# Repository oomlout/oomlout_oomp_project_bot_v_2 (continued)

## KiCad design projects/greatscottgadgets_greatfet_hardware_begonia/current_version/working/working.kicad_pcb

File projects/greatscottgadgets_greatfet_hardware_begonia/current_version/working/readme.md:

# greatfet_hardware
 
## summary 
* id: greatscottgadgets_greatfet_hardware_begonia
* user: greatscottgadgets
* name: greatfet_hardware
* board: begonia
* repo: https://github.com/greatscottgadgets/greatfet-hardware
* src_file_repo_kicad_pcb: begonia/begonia.kicad_pcb
* src_file_repo_kicad_pcb_link: https://github.com/greatscottgadgets/greatfet-hardware/tree/master/begonia/begonia.kicad_pcb

* src_file_repo_sch: begonia/begonia.sch
* src_file_repo_sch_link: https://github.com/greatscottgadgets/greatfet-hardware/tree/master/begonia/begonia.sch
* full details link: https://github.com/oomlout/oomlout_oomp_project_bot_v_2/tree/main/projects/greatscottgadgets_greatfet_hardware_begonia/current_version/working

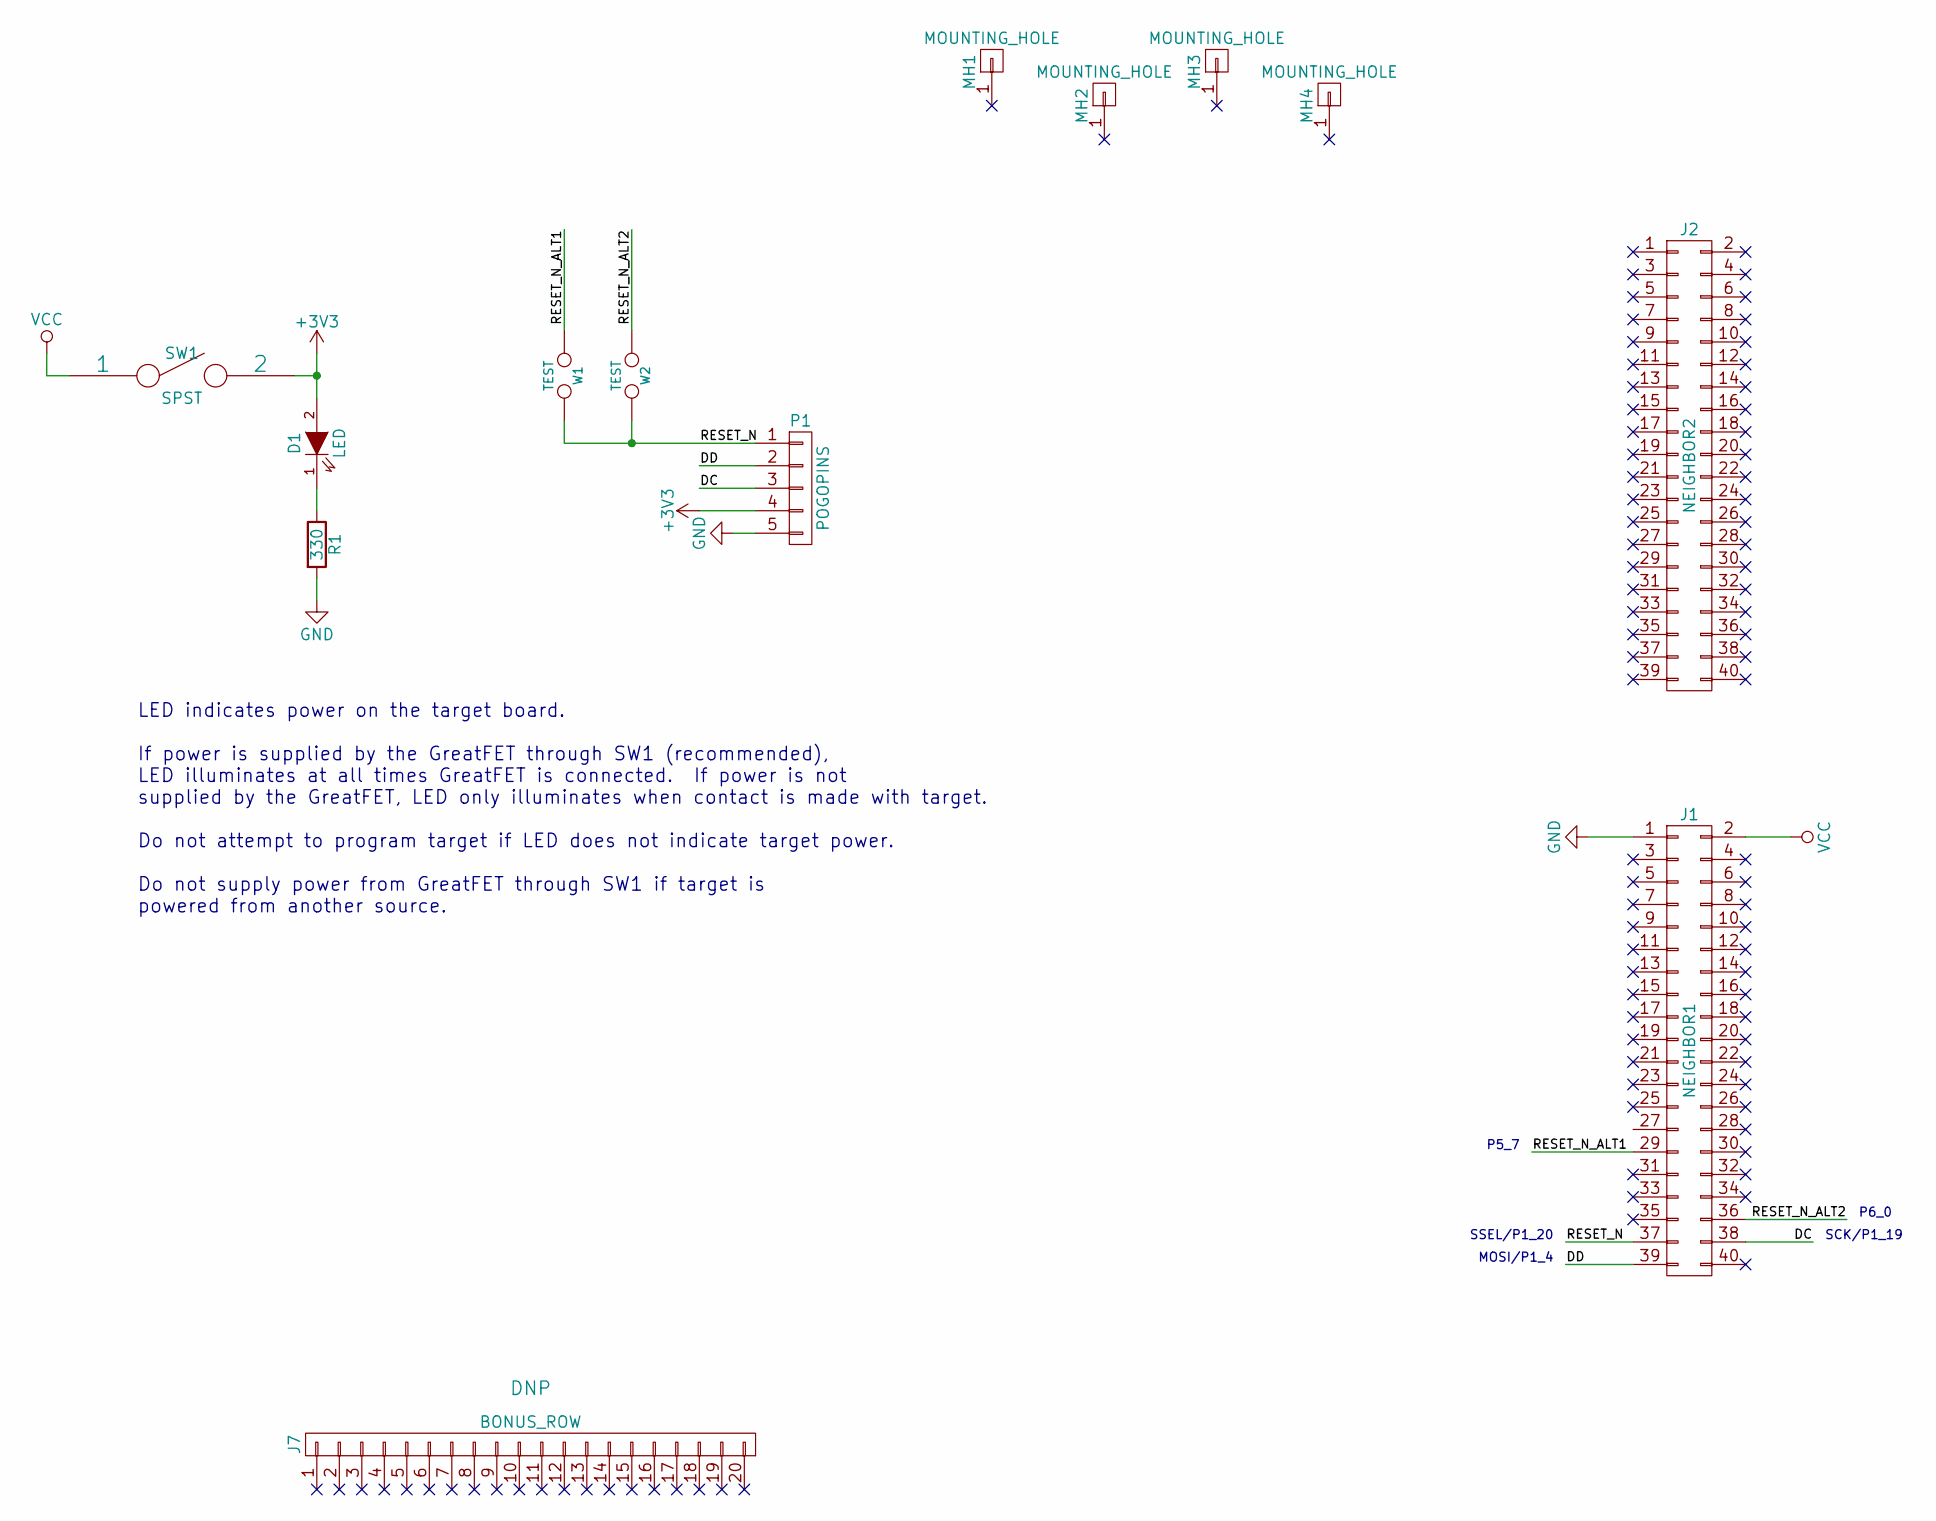
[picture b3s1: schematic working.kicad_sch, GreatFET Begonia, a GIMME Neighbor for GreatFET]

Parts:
D1: LED; 0603D; Part Number APT1608SGC
J1: NEIGHBOR1; HEADER-2x20; Part Number SSQ-120-23-G-D
J2: NEIGHBOR2; HEADER-2x20; Part Number SSQ-120-23-G-D
J7: BONUS_ROW; HEADER-1x20; Part Number SSQ-120-23-G-S
MH1, MH2, MH3, MH4: MOUNTING_HOLE; HOLE126MIL-COPPER
P1: POGOPINS; POGOPIN-5-IMME; Part Number PRT-09174
R1: 330; 0603; Part Number RMCF0603JT330R
SW1: SPST; SSSS810701; Part Number SSSS810701
W1, W2: TEST; 0603-JUMPER

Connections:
+3V3: D1.2 (A), P1.4, SW1.2
/DC: J1.38, P1.3
/DD: J1.39, P1.2
/RESET_N: J1.37, P1.1, W1.2, W2.2
/RESET_N_ALT1: J1.29, W1.1
/RESET_N_ALT2: J1.36, W2.1
GND: J1.1, P1.5, R1.2
unnamed: D1.1 (K), R1.1
VCC: J1.2, SW1.1

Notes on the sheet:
SSEL/P1_20
P6_0
P5_7
MOSI/P1_4
SCK/P1_19
LED indicates power on the target board. If power is supplied by the GreatFET through SW1 (recommended), LED illuminates at all times GreatFET is connected. If power is not supplied by the GreatFET, LED only illuminates when contact is made with target. Do not attempt to program target if LED does 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

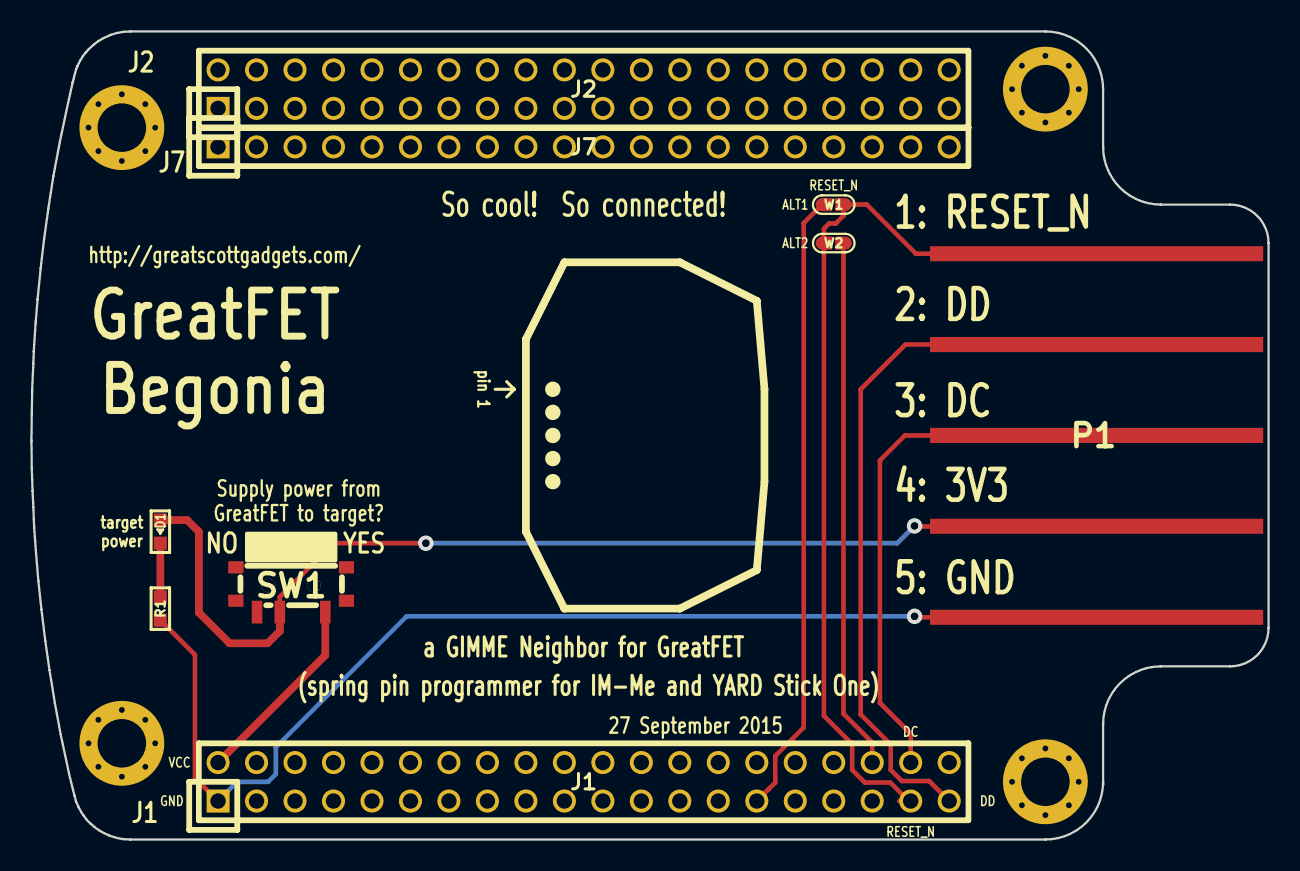
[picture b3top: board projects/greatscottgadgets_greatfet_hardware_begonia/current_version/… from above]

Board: 2 copper layers, 81.7 x 53.3 mm, 13 parts (0 on the bottom side), 9 nets.

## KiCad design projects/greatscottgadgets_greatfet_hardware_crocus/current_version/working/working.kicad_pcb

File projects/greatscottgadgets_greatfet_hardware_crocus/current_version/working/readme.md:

# greatfet_hardware
 
## summary 
* id: greatscottgadgets_greatfet_hardware_crocus
* user: greatscottgadgets
* name: greatfet_hardware
* board: crocus
* repo: https://github.com/greatscottgadgets/greatfet-hardware
* src_file_repo_kicad_pcb: crocus/crocus.kicad_pcb
* src_file_repo_kicad_pcb_link: https://github.com/greatscottgadgets/greatfet-hardware/tree/master/crocus/crocus.kicad_pcb

* src_file_repo_sch: crocus/crocus.sch
* src_file_repo_sch_link: https://github.com/greatscottgadgets/greatfet-hardware/tree/master/crocus/crocus.sch
* full details link: https://github.com/oomlout/oomlout_oomp_project_bot_v_2/tree/main/projects/greatscottgadgets_greatfet_hardware_crocus/current_version/working

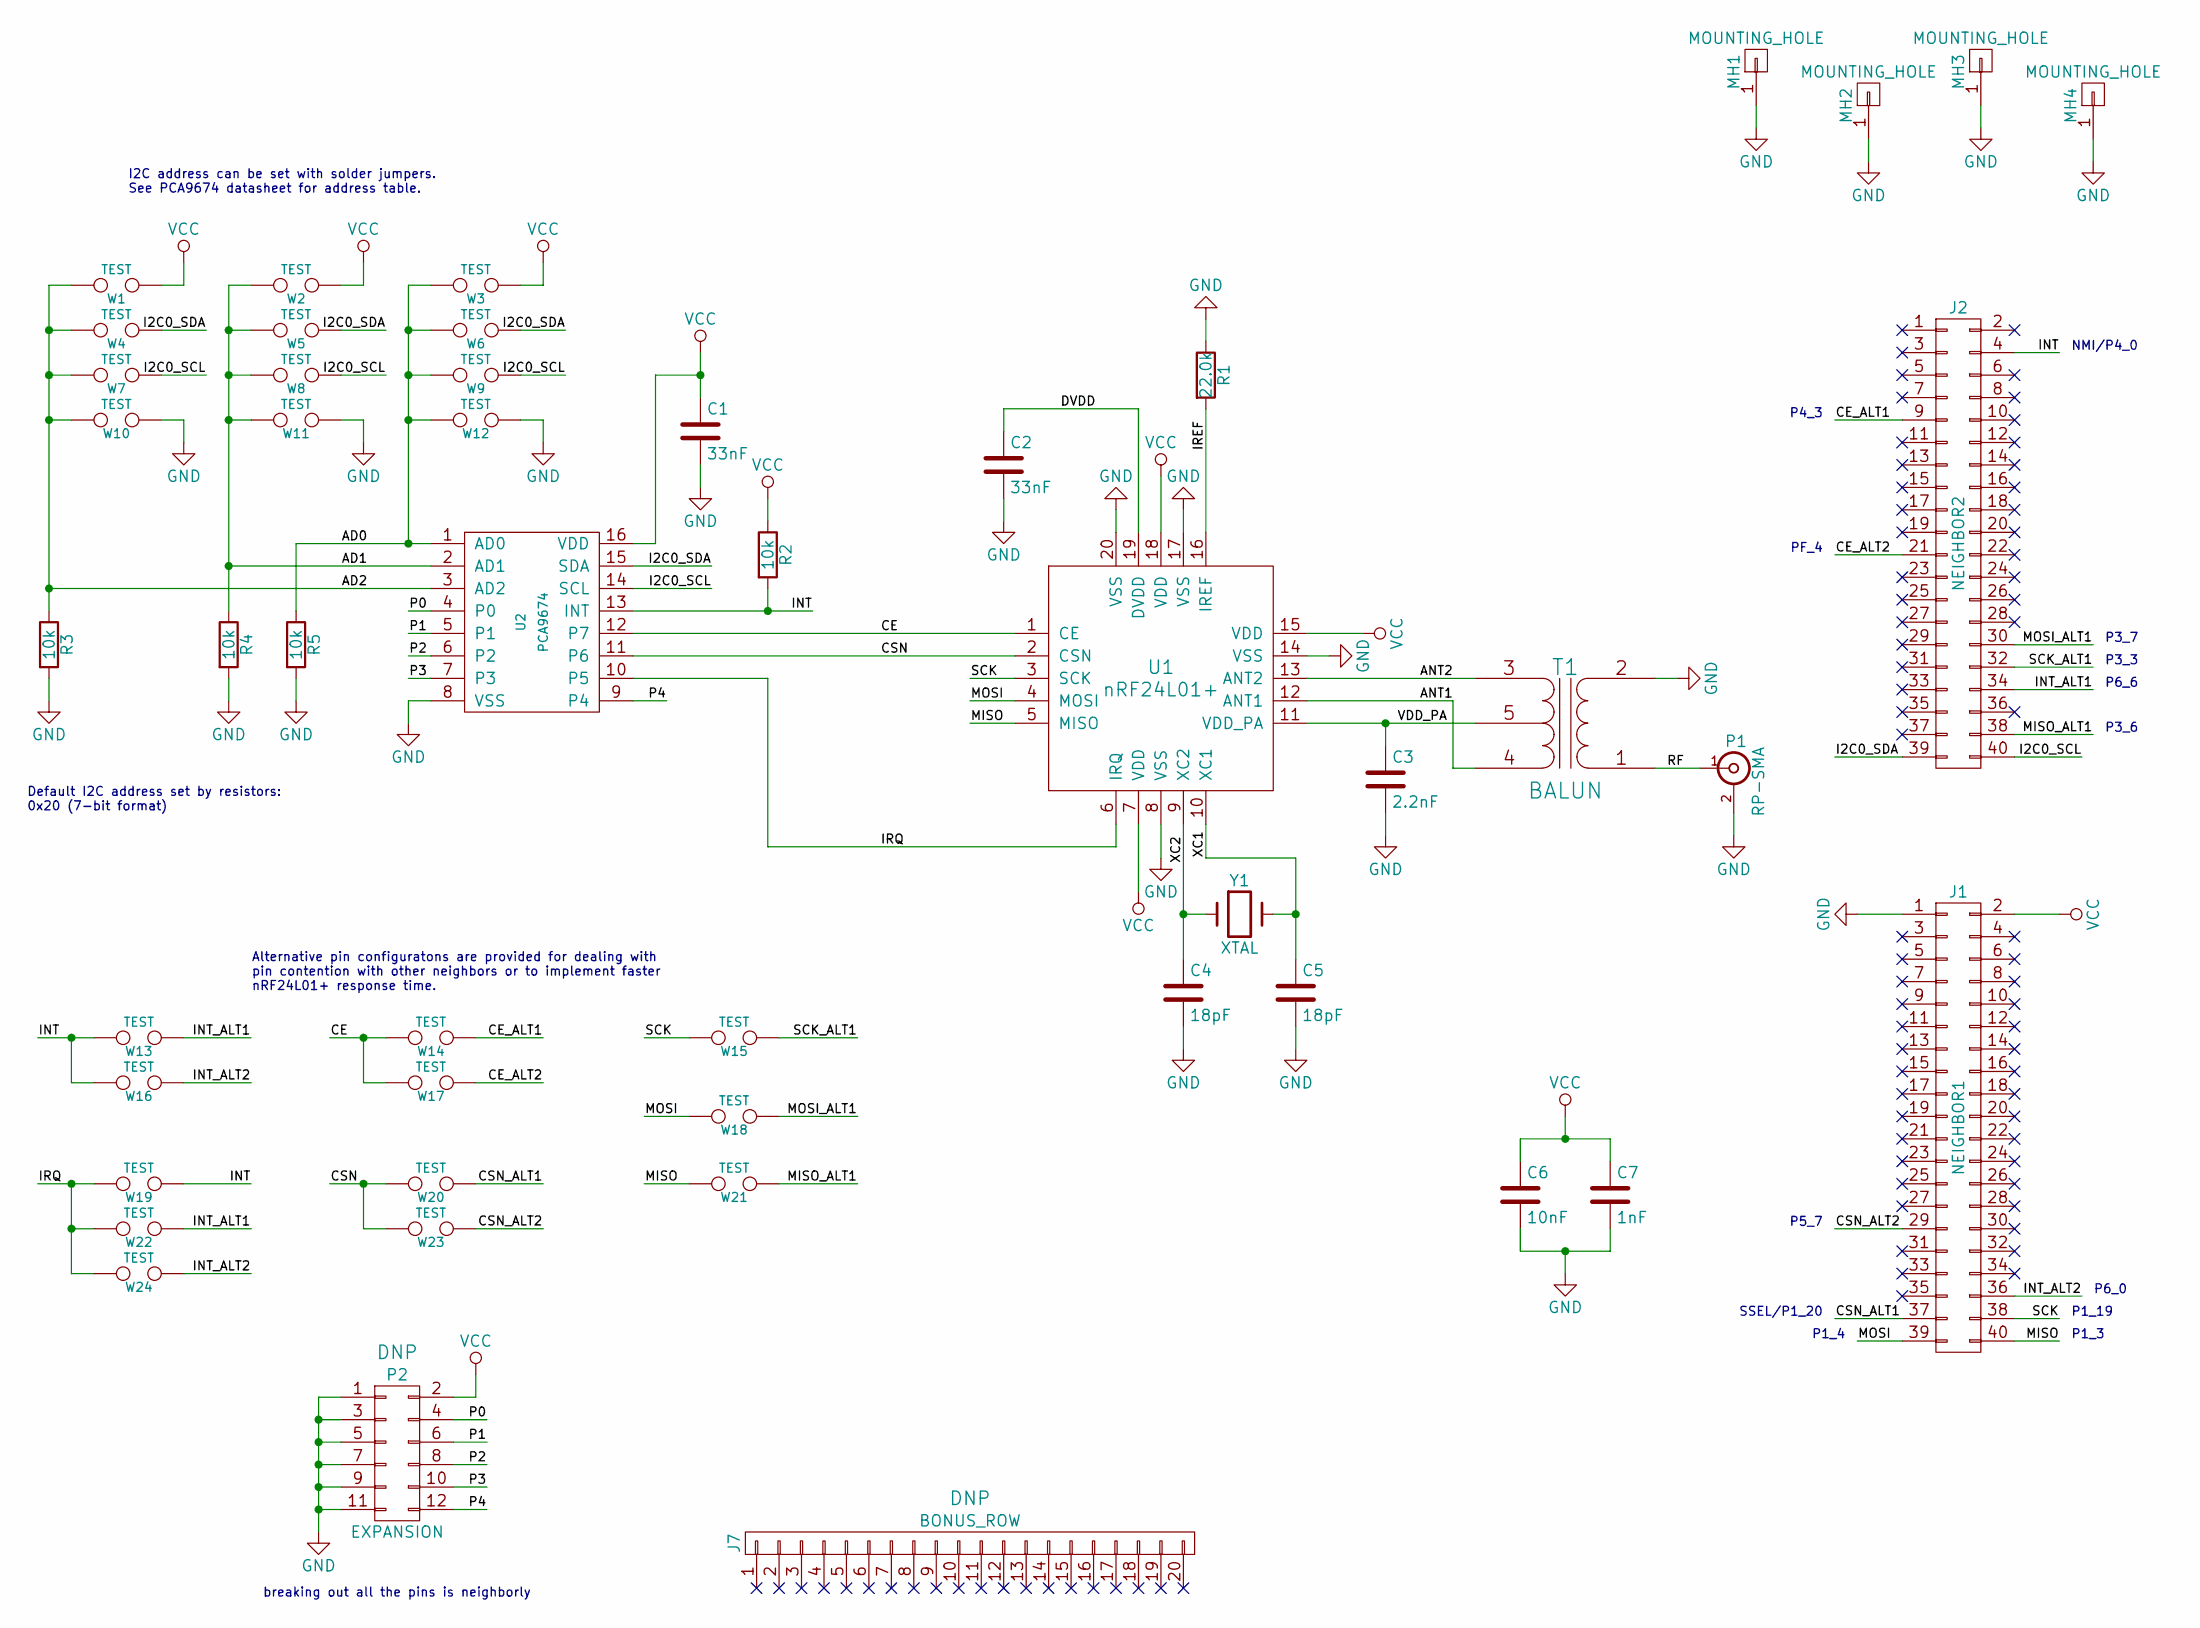
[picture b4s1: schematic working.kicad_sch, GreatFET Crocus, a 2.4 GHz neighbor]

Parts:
C1, C2: 33nF; 0603; Part Number CL10B333KB8SFNC
C3: 2.2nF; 0603; Part Number GRM188R71H222KA01D
C4, C5: 18pF; 0603; Part Number GRM1885C1H180JA01D
C6: 10nF; 0603; Part Number GRM188R71H103KA01D
C7: 1nF; 0603; Part Number GRM188R71H102KA01D
J1: NEIGHBOR1; HEADER-2x20; Part Number SSQ-120-23-G-D
J2: NEIGHBOR2; HEADER-2x20; Part Number SSQ-120-23-G-D
J7: BONUS_ROW; HEADER-1x20; Part Number SSQ-120-23-G-S
MH1, MH2, MH3, MH4: MOUNTING_HOLE; HOLE126MIL-COPPER
P1: RP-SMA; SMA-EDGE; Part Number CONREVSMA003.031
P2: EXPANSION; HEADER-2x6
R1: 22.0k; 0603; Part Number RMCF0603FT22K0
R2, R3, R4, R5: 10k; 0603; Part Number ERJ-3GEYJ103V
T1: BALUN; 2500BL14M100; Part Number 2450BM14A0002T
U1: nRF24L01+; QFN20-4; Part Number NRF24L01P-R7
U2: PCA9674; TSSOP16; Part Number PCA9674PW,118
W1, W2, W3, W4, W5, W6, W7, W8, W9, W10, W11, W12, W13, W14, W15, W16, W17, W18, W19, W20, W21, W22, W23, W24: TEST; 0603-JUMPER
Y1: XTAL; HC-49S; Part Number 9C-16.000MAAE-T

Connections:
/AD0: R5.1, U2.1 (AD0), W3.2, W6.2, W9.2, W12.2
/AD1: R4.1, U2.2 (AD1), W2.2, W5.2, W8.2, W11.2
/AD2: R3.1, U2.3 (AD2), W1.2, W4.2, W7.2, W10.2
/ANT1: T1.4 (PR2), U1.12 (ANT1)
/ANT2: T1.3 (PR1), U1.13 (ANT2)
/CE: U1.1 (CE), U2.12 (P7), W14.2, W17.2
/CE_ALT1: J2.9, W14.1
/CE_ALT2: J2.21, W17.1
/CSN: U1.2 (CSN), U2.11 (P6), W20.2, W23.2
/CSN_ALT1: J1.37, W20.1
/CSN_ALT2: J1.29, W23.1
/DVDD: C2.1, U1.19 (DVDD)
/I2C0_SCL: J2.40, U2.14 (SCL), W7.1, W8.1, W9.1
/I2C0_SDA: J2.39, U2.15 (SDA), W4.1, W5.1, W6.1
/INT: J2.4, R2.2, U2.13 (INT), W13.2, W16.2, W19.1
/INT_ALT1: J2.34, W13.1, W22.1
/INT_ALT2: J1.36, W16.1, W24.1
/IREF: R1.2, U1.16 (IREF)
/IRQ: U1.6 (IRQ), U2.10 (P5), W19.2, W22.2, W24.2
/MISO: J1.40, U1.5 (MISO), W21.2
/MISO_ALT1: J2.38, W21.1
/MOSI: J1.39, U1.4 (MOSI), W18.2
/MOSI_ALT1: J2.30, W18.1
/P0: P2.4, U2.4 (P0)
/P1: P2.6, U2.5 (P1)
/P2: P2.8, U2.6 (P2)
/P3: P2.10, U2.7 (P3)
/P4: P2.12, U2.9 (P4)
/RF: P1.1 (In), T1.1 (S1)
/SCK: J1.38, U1.3 (SCK), W15.2
/SCK_ALT1: J2.32, W15.1
/VDD_PA: C3.1, T1.5 (PM), U1.11 (VDD_PA)
/XC1: C5.1, U1.10 (XC1), Y1.2
/XC2: C4.1, U1.9 (XC2), Y1.1
GND: C1.2, C2.2, C3.2, C4.2, C5.2, C6.2, C7.2, J1.1, MH1.1, MH2.1, MH3.1, MH4.1, P1.2 (Ext), P2.1, P2.3, P2.5, P2.7, P2.9, P2.11, R1.1, R3.2, R4.2, R5.2, T1.2 (S2), U1.8 (VSS), U1.14 (VSS), U1.17 (VSS), U1.20 (VSS), U2.8 (VSS), W10.1, W11.1, W12.1
VCC: C1.1, C6.1, C7.1, J1.2, P2.2, R2.1, U1.7 (VDD), U1.15 (VDD), U1.18 (VDD), U2.16 (VDD), W1.1, W2.1, W3.1

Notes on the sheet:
P6_0
P1_19
I2C address can be set with solder jumpers. See PCA9674 datasheet for address table.
P1_3
PF_4
NMI/P4_0
Alternative pin configuratons are provided for dealing with pin contention with other neighbors or to implement faster nRF24L01+ response time.
SSEL/P1_20
breaking out all the pins is neighborly
P1_4
Default I2C address set by resistors: 0x20 (7-bit format)
P3_6
P4_3
P5_7
P3_3
P3_7
P6_6

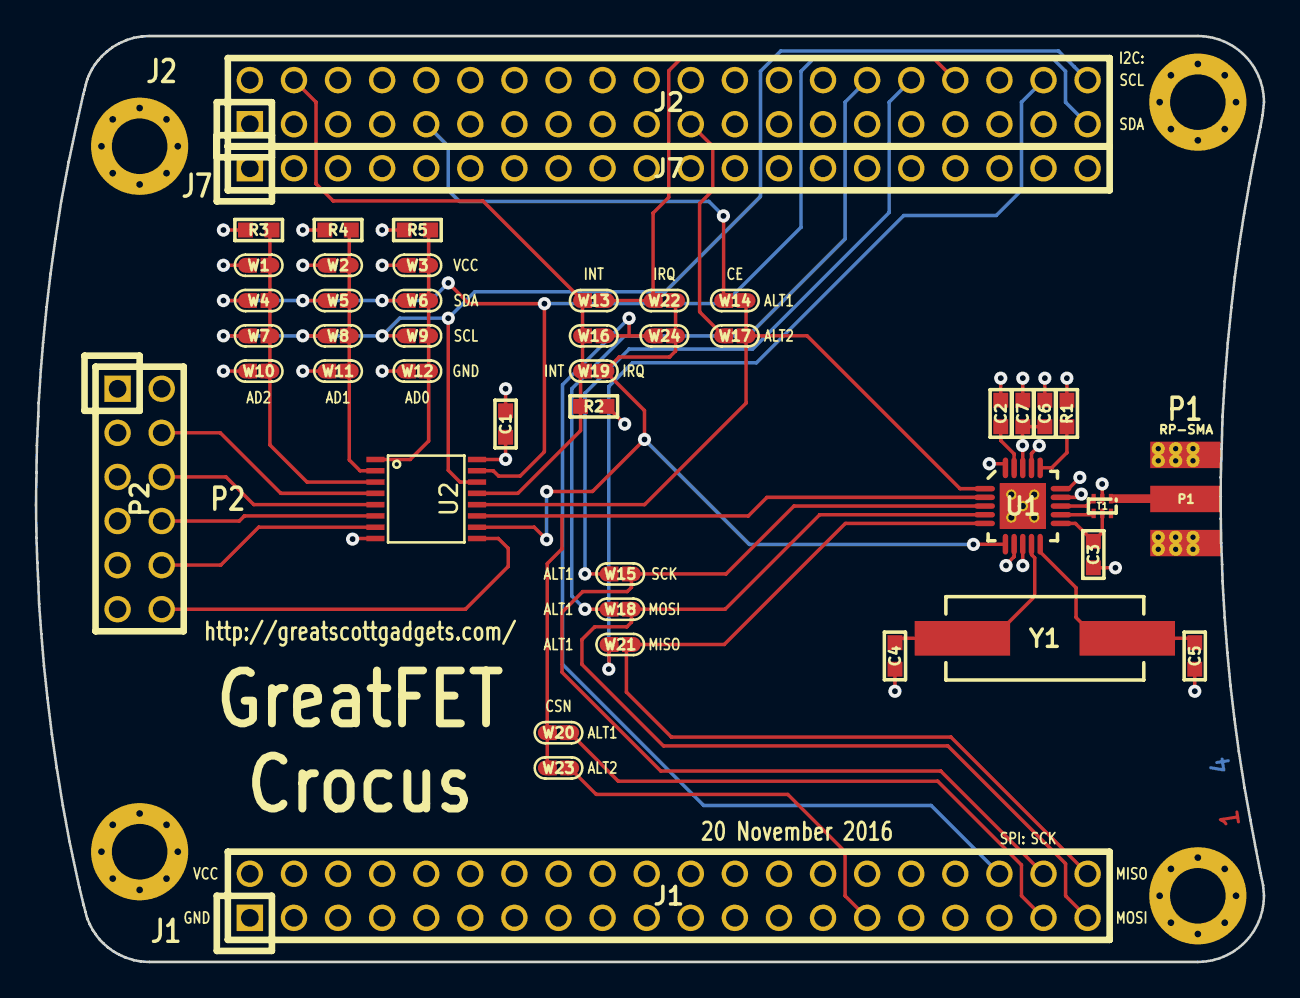
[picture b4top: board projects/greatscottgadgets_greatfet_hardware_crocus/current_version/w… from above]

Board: 4 copper layers, 70.7 x 53.3 mm, 49 parts (0 on the bottom side), 36 nets.

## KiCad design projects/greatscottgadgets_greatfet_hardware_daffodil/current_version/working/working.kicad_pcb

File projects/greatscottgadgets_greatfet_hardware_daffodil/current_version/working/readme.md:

# greatfet_hardware
 
## summary 
* id: greatscottgadgets_greatfet_hardware_daffodil
* user: greatscottgadgets
* name: greatfet_hardware
* board: daffodil
* repo: https://github.com/greatscottgadgets/greatfet-hardware
* src_file_repo_kicad_pcb: daffodil/daffodil.kicad_pcb
* src_file_repo_kicad_pcb_link: https://github.com/greatscottgadgets/greatfet-hardware/tree/master/daffodil/daffodil.kicad_pcb

* src_file_repo_sch: daffodil/daffodil.sch
* src_file_repo_sch_link: https://github.com/greatscottgadgets/greatfet-hardware/tree/master/daffodil/daffodil.sch
* full details link: https://github.com/oomlout/oomlout_oomp_project_bot_v_2/tree/main/projects/greatscottgadgets_greatfet_hardware_daffodil/current_version/working

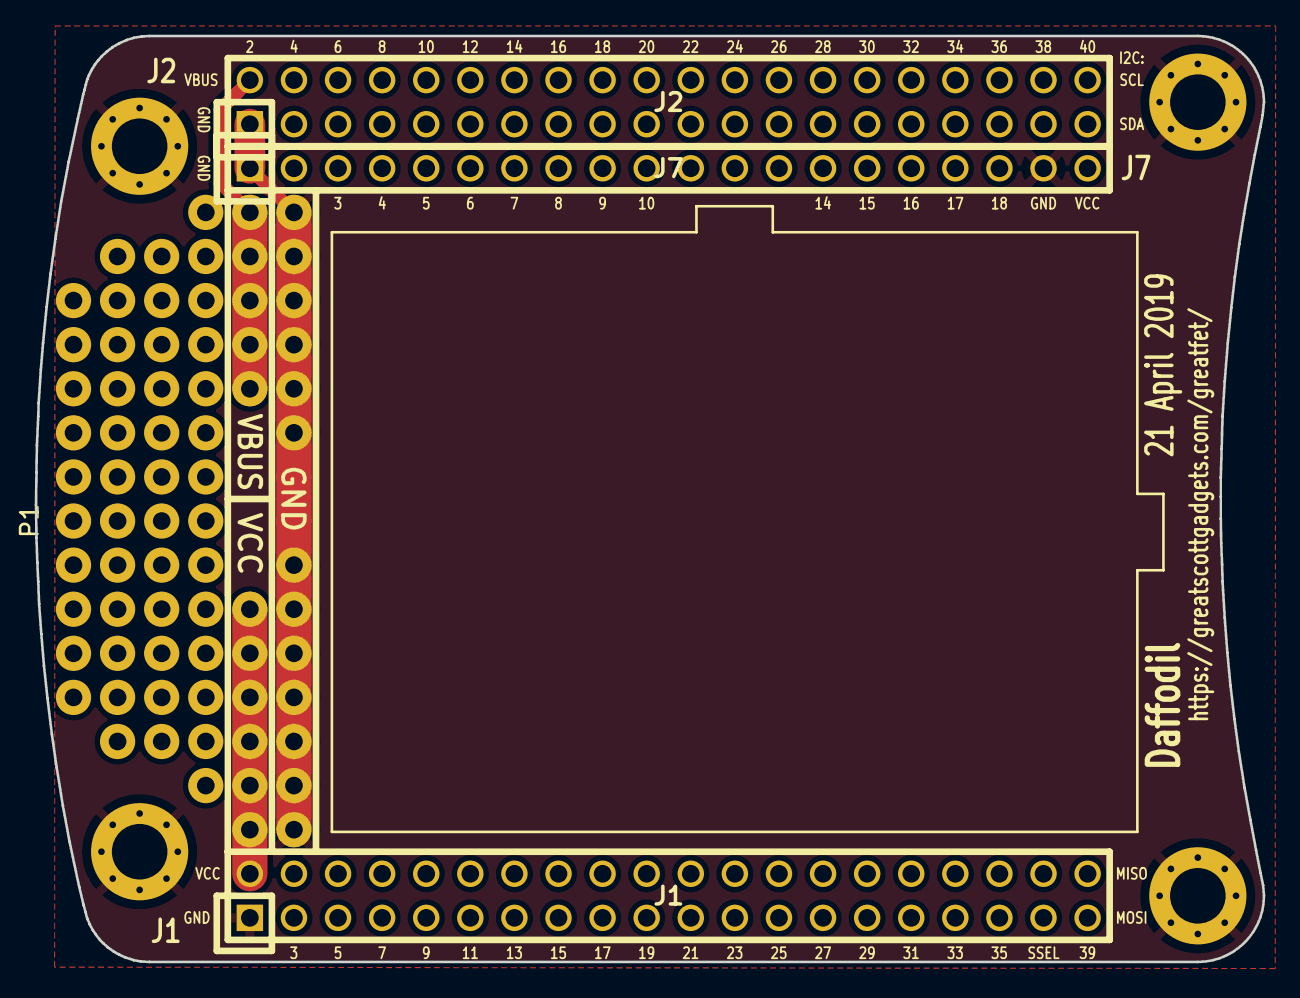
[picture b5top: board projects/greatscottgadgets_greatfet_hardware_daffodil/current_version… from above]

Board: 2 copper layers, 70.7 x 53.3 mm, 8 parts (0 on the bottom side), 3 nets.

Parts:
J1: NEIGHBOR1; HEADER-2x20
J2: NEIGHBOR2; HEADER-2x20
J7: BONUS_ROW; HEADER-1x20
MH1, MH2, MH3, MH4: MOUNTING_HOLE; HOLE126MIL-COPPER
P1: GREATFET-PROTO-AREA

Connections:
/VBUS: J2.2, P1.14, P1.15, P1.16, P1.17, P1.18
GND: J1.1, J2.1, J7.1, J7.19, MH1.1, MH2.1, MH3.1, MH4.1, P1.1, P1.2, P1.3, P1.4, P1.5, P1.6, P1.7, P1.8, P1.9, P1.10, P1.11, P1.12, P1.13
VCC: J1.2, J7.20, P1.19, P1.20, P1.21, P1.22, P1.23, P1.24

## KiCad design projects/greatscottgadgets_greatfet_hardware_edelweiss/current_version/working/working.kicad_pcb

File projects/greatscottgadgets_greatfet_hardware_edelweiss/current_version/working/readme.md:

# greatfet_hardware
 
## summary 
* id: greatscottgadgets_greatfet_hardware_edelweiss
* user: greatscottgadgets
* name: greatfet_hardware
* board: edelweiss
* repo: https://github.com/greatscottgadgets/greatfet-hardware
* src_file_repo_kicad_pcb: edelweiss/edelweiss.kicad_pcb
* src_file_repo_kicad_pcb_link: https://github.com/greatscottgadgets/greatfet-hardware/tree/master/edelweiss/edelweiss.kicad_pcb

* src_file_repo_sch: edelweiss/edelweiss.sch
* src_file_repo_sch_link: https://github.com/greatscottgadgets/greatfet-hardware/tree/master/edelweiss/edelweiss.sch
* full details link: https://github.com/oomlout/oomlout_oomp_project_bot_v_2/tree/main/projects/greatscottgadgets_greatfet_hardware_edelweiss/current_version/working

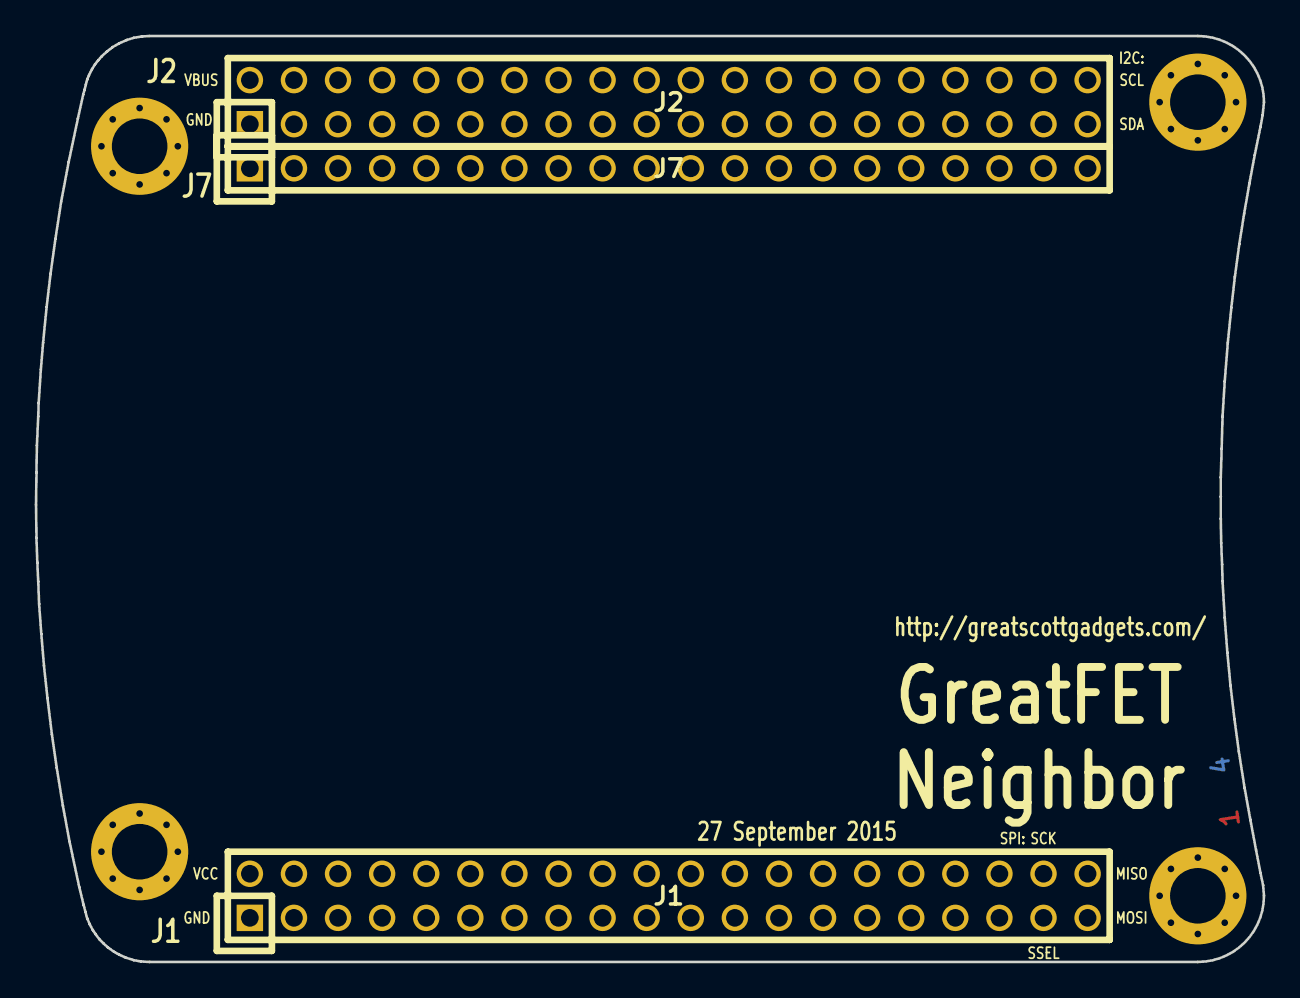
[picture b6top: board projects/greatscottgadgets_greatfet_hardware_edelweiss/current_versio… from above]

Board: 4 copper layers, 70.7 x 53.3 mm, 7 parts (0 on the bottom side), 2 nets, no tracks yet.

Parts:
J1: NEIGHBOR1; HEADER-2x20
J2: NEIGHBOR2; HEADER-2x20
J7: BONUS_ROW; HEADER-1x20
MH1, MH2, MH3, MH4: MOUNTING_HOLE; HOLE126MIL-COPPER

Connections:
GND: J1.1, J2.1, J7.1, J7.10, J7.19, MH1.1, MH2.1, MH3.1, MH4.1
VCC: J1.2, J7.20

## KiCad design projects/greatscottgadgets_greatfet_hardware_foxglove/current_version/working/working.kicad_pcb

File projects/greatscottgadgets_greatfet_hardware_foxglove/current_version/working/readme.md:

# greatfet_hardware
 
## summary 
* id: greatscottgadgets_greatfet_hardware_foxglove
* user: greatscottgadgets
* name: greatfet_hardware
* board: foxglove
* repo: https://github.com/greatscottgadgets/greatfet-hardware
* src_file_repo_kicad_pcb: foxglove/foxglove.kicad_pcb
* src_file_repo_kicad_pcb_link: https://github.com/greatscottgadgets/greatfet-hardware/tree/master/foxglove/foxglove.kicad_pcb

* src_file_repo_sch: foxglove/foxglove.sch
* src_file_repo_sch_link: https://github.com/greatscottgadgets/greatfet-hardware/tree/master/foxglove/foxglove.sch
* full details link: https://github.com/oomlout/oomlout_oomp_project_bot_v_2/tree/main/projects/greatscottgadgets_greatfet_hardware_foxglove/current_version/working

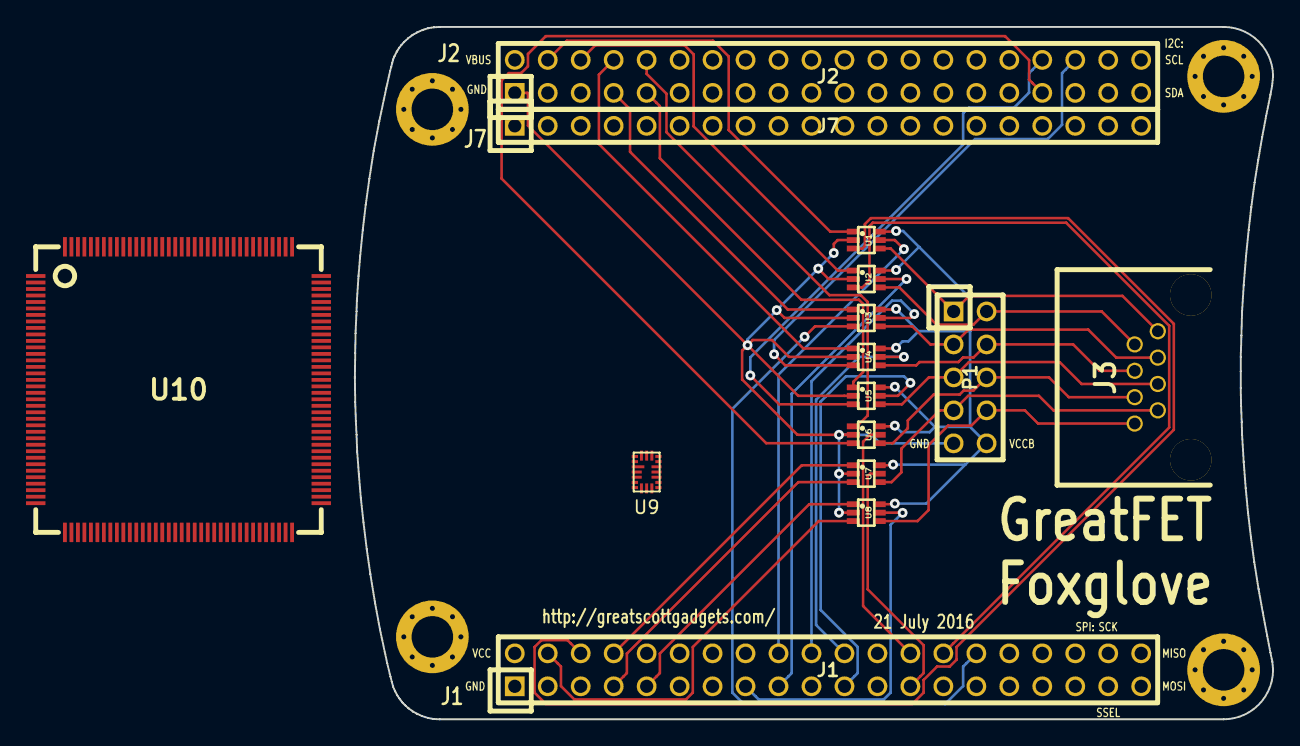
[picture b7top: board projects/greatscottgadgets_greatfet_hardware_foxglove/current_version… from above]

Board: 2 copper layers, 70.7 x 53.3 mm, 19 parts (0 on the bottom side), 35 nets.

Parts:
J1: NEIGHBOR1; HEADER-2x20
J2: NEIGHBOR2; HEADER-2x20
J3: RJ45; RJ45-RJHSE-5380
J7: BONUS_ROW; HEADER-1x20
MH1, MH2, MH3, MH4: MOUNTING_HOLE; HOLE126MIL-COPPER
P1: CONN_02X05; HEADER-2x5
U1: SHIFTER1; SOT363
U2: SHIFTER2; SOT363
U3: SHIFTER3; SOT363
U4: SHIFTER4; SOT363
U5: SHIFTER5; SOT363
U6: SHIFTER6; SOT363
U7: SHIFTER7; SOT363
U8: SHIFTER8; SOT363
U9: SLG46621
U10: iCE40HX4K; LQFP144

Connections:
/A1: J1.6, U1.3
/A2: J1.28, U2.3
/A3: J1.30, U3.3
/A4: J2.36, U4.3
/A5: J2.34, U5.3
/A6: J2.33, U6.3
/A7: J1.7, U7.3
/A8: J1.4, U8.3
/B1: J3.1, P1.1, U1.4
/B2: J3.2, P1.2, U2.4
/B3: J3.3, P1.3, U3.4
/B4: J3.4, P1.4, U4.4
/B5: J3.5, P1.5, U5.4
/B6: J3.6, P1.6, U6.4
/B7: J3.7, P1.7, U7.4
/B8: J3.8, P1.8, U8.4
/DIR1: J1.18, U1.5
/DIR2: J1.17, U2.5
/DIR3: J1.20, U3.5
/DIR4: J1.22, U4.5
/DIR5: J1.21, U5.5
/DIR6: J1.26, U6.5
/DIR7: J1.25, U7.5
/DIR8: J1.15, U8.5
/VA1: J2.4, U1.1
/VA2: J2.6, U2.1
/VA3: J2.7, U3.1
/VA4: J2.8, U4.1
/VA5: J2.9, U5.1
/VA6: J2.10, U6.1
/VA7: J1.8, U7.1
/VA8: J1.9, U8.1
/VCCB: P1.10, U1.6, U2.6, U3.6, U4.6, U5.6, U6.6, U7.6, U8.6
GND: J1.1, J2.1, MH1.1, MH2.1, MH3.1, MH4.1, P1.9, U1.2, U2.2, U3.2, U4.2, U5.2, U6.2, U7.2, U8.2, U9.11
VCC: J1.2, U9.1

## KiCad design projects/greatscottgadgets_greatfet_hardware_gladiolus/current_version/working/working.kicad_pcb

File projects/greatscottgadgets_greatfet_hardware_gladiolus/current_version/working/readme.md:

# greatfet_hardware
 
## summary 
* id: greatscottgadgets_greatfet_hardware_gladiolus
* user: greatscottgadgets
* name: greatfet_hardware
* board: gladiolus
* repo: https://github.com/greatscottgadgets/greatfet-hardware
* src_file_repo_kicad_pcb: gladiolus/gladiolus.kicad_pcb
* src_file_repo_kicad_pcb_link: https://github.com/greatscottgadgets/greatfet-hardware/tree/master/gladiolus/gladiolus.kicad_pcb

* src_file_repo_sch: gladiolus/gladiolus.sch
* src_file_repo_sch_link: https://github.com/greatscottgadgets/greatfet-hardware/tree/master/gladiolus/gladiolus.sch
* full details link: https://github.com/oomlout/oomlout_oomp_project_bot_v_2/tree/main/projects/greatscottgadgets_greatfet_hardware_gladiolus/current_version/working

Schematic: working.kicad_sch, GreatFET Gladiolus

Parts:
C1, C4: C; 0603
C2, C10, C26: 15pF; 0402; Part Number GRM1555C1H150GA01D
C3, C5, C6, C7, C11, C12, C13, C17, C18, C19, C20, C21, C22, C23, C24, C25, C27: 100nF; 0603; Part Number GRM188R71C104KA01D
C8: 10uF; 0805; Part Number GRM21BR61A106KE19L
C9: 100pF; 0402; Part Number GRM1555C1H101GA01D
C14: 130pF; 0402; Part Number GRM1555C1H131GA01D
C15: 82pF; 0402; Part Number GRM1555C1H820GA01D
C16: 24pF; 0402; Part Number GRM1555C1H240GA01D
C28: 8nF; 0603; Part Number GRM1555C1H150GA01D
C29: 470pF; 0402; Part Number GCM155R71H471KA37D
D1: PHOTODIODE; LED-3MM; Part Number PD204-6B
D2: PHOTODIODE; VBPW34FASR; Part Number VBPW34FASR
D3: LED; LED-5MM; Part Number TSHF5210
FB1: FILTER; 0805; Part Number BLM21PG221SN1D
J1: NEIGHBOR1; HEADER-2x20; Part Number SSQ-120-23-G-D
J2: NEIGHBOR2; HEADER-2x20; Part Number SSQ-120-23-G-D
J3: Conn_01x02_Female; HEADER-1x2
J7: BONUS_ROW; HEADER-1x20; Part Number SSQ-120-23-G-S
L1, L2, L5, L6, L7, L8: 2.2uH; 0402; Part Number MLF1005G2R2JT000
L3, L4: 1.5uH; 0402; Part Number MLF1005G1R5KT000
L9, L10: 1uH; 0402; Part Number MLF1005G1R0JT000
MH1, MH2, MH3, MH4: MOUNTING_HOLE; HOLE126MIL-COPPER
Q1: Q_NPN_BEC; SOT23-3; Part Number BSV52
R1, R2, R3, R4, R9, R19, R20, R21, R22, R23, R26, R29, R31, R38, R39, R40, R41, R42, R43, R44, R45, R64, R67, R72, R74, R77: 0; 0603; Part Number RC0603JR-070RL
R5, R11, R12, R13, R14, R37, R56: R; 0603
R6: 100k; 0402; Part Number RC0402FR-07100KL
R7: 3.24k; 0603; Part Number RC0603FR-073K24L
R8: 1.74k; 0603; Part Number RC0603FR-071K74L
R10, R27, R36, R55, R58, R59, R60, R61, R62, R63: 10k; 0603; Part Number ERJ-3GEYJ103V
R15, R16, R32, R33: 0; 0402; Part Number RC0402JR-070RL
R17, R18, R34, R35: R; 0402
R24, R25, R73: 1k; 0603; Part Number RC0603JR-071KL
R28, R46, R47, R48, R49, R50, R51, R52, R53, R54: 39; 0603; Part Number RC0603JR-0739RL
R30: 75; 0603; Part Number RC0603FR-0775RL
R57: 20k; 0603; Part Number RC0603JR-0720KL
R66, R69: 249; 0603; Part Number 311-249HR
R70: 1.80k; 0603; Part Number RC0603FR-071K8L
R71: 953; 0603; Part Number RC0603FR-07953RL
R75: 12k; 0603; Part Number RC0603JR-0712KL
R76: 1M; 0603
R78: 0; 0603
RV1, RV2, RV3: POT; 3306F; Part Number 3306F-1-103
U1: THS4520RGT; QFN16-3; Part Number THS4520RGT
U2: AD8330ARQZ; TSSOP16; Part Number AD8330ARQZ
U3: AD9283; SSOP20; Part Number AD9283BRSZ-50
U4: AD9704; QFN32-5; Part Number AD9704BCPZ
U5: LMH6643; VSSOP8; Part Number LMH6643MM
U6, U7: 74LVC1G3157; SOT363; Part Number 74LVC1G3157DW-7

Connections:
/ADC0_0: J2.5, R21.2, R64.2
/ADCCLK: R37.1, R46.1, U3.10
/D0: R38.2, U3.20
/D1: R39.2, U3.19
/D2: R40.2, U3.18
/D3: R41.2, U3.17
/D4: R42.2, U3.14
/D5: R43.2, U3.13
/D6: R44.2, U3.12
/D7: R45.2, U3.11
/DACCLK: R54.1, R56.1, U4.12
/P0_0: J1.4, R38.1
/P0_1: J1.6, R39.1
/P1_0: J1.7, R45.1
/P1_5: J1.13, R24.2
/P1_6: J1.16, R54.2
/P1_7: J1.15, R53.2
/P1_8: J1.18, R52.2
/P1_9: J1.17, R51.2
/P1_10: J1.20, R50.2
/P1_11: J1.22, R49.2
/P1_12: J1.21, R48.2
/P1_13: J1.26, R47.2
/P1_14: J1.25, R28.2
/P1_15: J1.28, R40.1
/P1_16: J1.30, R41.1
/P2_1: J2.35, R78.1
/P2_2: J2.33, R44.1
/P2_3: J2.20, R36.1, U3.1
/P2_5: J2.18, R9.2, R10.2, R19.1
/P3_5: J2.37, R77.2
/P4_3: J2.9, R29.2
/P4_4: J2.7, R22.2
/P4_8: J2.3, R26.2
/P5_0: J1.8, R55.2, U4.25, U7.6
/P5_2: J1.14, R58.2, R59.1, U4.15
/P5_3: J1.19, R60.2, R61.1, U4.16
/P5_5: J1.23, R62.2, R63.1, U4.17
/P5_6: J1.27, R25.2
/P6_3: J2.36, R42.1
/P6_6: J2.34, R43.1
/P9_6: J1.34, R46.2
/RXIN: C28.1, D1.2 (A), D2.2 (A), R5.1, R76.1, U6.4
/TXOUT: D3.1, Q1.3 (C)
/VBUS: J2.2, R3.2
GND: C1.2, C3.2, C5.2, C6.2, C7.2, C8.2, C11.2, C12.2, C13.2, C17.1, C18.1, C19.1, C20.1, C21.2, C22.2, C23.2, C24.1, C25.2, C27.2, J1.1, J2.1, J3.2, J7.1, J7.10, J7.19, MH1.1, MH2.1, MH3.1, MH4.1, R4.2, R8.1, R10.1, R14.2, R17.1, R18.2, R20.2, R27.2, R30.2, R34.1, R35.2, R37.2, R56.2, R57.1, R59.2, R61.2, R63.2, R66.2, R70.2, R76.2, RV1.1, RV2.1, RV3.1, U1.0, U1.13, U1.14, U1.15, U1.16, U2.8, U2.9, U2.11, U3.4, U3.9, U3.16, U4.0, U4.10, U4.14, U4.19, U4.22, U4.26, U5.4, U6.2, U7.2
unnamed: C1.1, D1.1 (K), D2.1 (K), R1.2, R2.1, R3.1, R4.1
unnamed: C2.1, L1.2, R6.1, U1.10
unnamed: C2.2, C28.2, R6.2, U1.11, U6.1
unnamed: C3.1, C4.2, R1.1, R7.1, R8.2, R11.1, R12.1, RV1.2, U1.2
unnamed: C4.1, L2.2, R11.2, U1.3
unnamed: C5.1, R5.2, U1.9
unnamed: C7.1, R12.2, R13.2, R14.1, U1.4
unnamed: C9.1, L1.1, L3.2
unnamed: C9.2, L2.1, L4.2
unnamed: C10.1, L3.1, R15.1
unnamed: C10.2, L4.1, R16.1
unnamed: C13.1, R31.1, U2.15
unnamed: C14.1, L5.1, L7.2
unnamed: C14.2, L6.1, L8.2
unnamed: C15.1, L7.1, L9.2
unnamed: C15.2, L8.1, L10.2
unnamed: C16.1, L9.1, R32.1
unnamed: C16.2, L10.1, R33.1
unnamed: C18.2, R31.2, U3.2, U3.3
unnamed: C24.2, R67.1, U4.23
unnamed: C25.1, R24.1, R25.1, R27.1, R67.2, U5.3, U7.1
unnamed: C26.1, R69.1, R70.1, R71.1, U5.2, U7.4
unnamed: C26.2, R71.2, R72.1, U5.1
unnamed: C29.1, R73.2, U5.7
unnamed: C29.2, R74.1, U5.6
unnamed: FB1.2, J1.2
unnamed: J3.1, Q1.2 (E), R30.1, R64.1, R74.2
unnamed: L5.2, U2.13
unnamed: L6.2, U2.12
unnamed: Q1.1 (B), R73.1
unnamed: R9.1, U1.12
unnamed: R15.2, R17.2, U2.4
unnamed: R16.2, R18.1, U2.5
unnamed: R19.2, U2.2
unnamed: R20.1, U2.1
unnamed: R21.1, R22.1, RV2.2, U2.7
unnamed: R23.1, R26.1, U2.6
unnamed: R28.1, U4.27
unnamed: R29.1, RV3.2, U2.10
unnamed: R32.2, R34.2, U3.6
unnamed: R33.2, R35.1, U3.7
unnamed: R47.1, U4.28
unnamed: R48.1, U4.29
unnamed: R49.1, U4.30
unnamed: R50.1, U4.31
unnamed: R51.1, U4.32
unnamed: R52.1, U4.1
unnamed: R53.1, U4.2
unnamed: R57.2, U4.24
unnamed: R66.1, U4.21
unnamed: R69.2, U4.20
unnamed: R72.2, U5.5
unnamed: R75.1, RV2.3
unnamed: R77.1, R78.2, U6.6
VCC: C6.1, C8.1, C11.1, C12.1, C17.2, C19.2, C20.2, C21.1, C22.1, C23.1, C27.1, D3.2, FB1.1, R2.2, R7.2, R13.1, R23.2, R36.2, R55.1, R58.1, R60.1, R62.1, R75.2, RV1.3, RV3.3, U1.5, U1.6, U1.7, U1.8, U2.3, U2.14, U2.16, U3.5, U3.8, U3.15, U4.3, U4.11, U4.18, U5.8, U6.5, U7.5

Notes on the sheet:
MOSI
GPIO1[8]
BOOT
short +/- inputs to turn off TX
SGPIO0
GPIO2[12]
MISO
GPIO1[9]
SGPIO7
SSEL
removed DNP components for inverting output
switch for ac/dc coupling ac coupled on logic low
GPIO1[1]
GPIO2[9]
GPIO1[7]
SCK
GPIO1[6]
GPIO2[15]
10 MHz LPF
SGPIO3
ISP
SGPIO1
GPIO1[4]
GPIO1[5]
^ This cap cuts off higher freqs (15MHz+) 470pF works well
SGPIO6
GPIO1[0]
SGPIO8
GPIO1[3]
SGPIO4
SGPIO5
GPIO2[14]
GPIO2[11]
TODO: DNP?
DFU
GPIO1[2]
Default configuration: pin mode unsigned binary single-ended clock
SGPIO2
